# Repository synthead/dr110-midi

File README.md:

# Synthead BOSS DR-110 MIDI Retrofit

This is an open, Arduino-based project that adds MIDI to your BOSS DR-110!

## Features

This retrofit supports:

- **MIDI sync** via MIDI start, stop, continue, and beat clock messages to play patterns programmed on the DR-110's internal sequencer in time.
- **MIDI note on** messages to play individual drum sounds in an external sequencer.  The General MIDI note mapping is followed.

## How it works

### MIDI sync

The START and STOP buttons on the front panel are "pressed" to MIDI start and stop messages, and a clock is generated to keep the internal sequencer in time with MIDI beat clock messages.  There is also a transistor on the retrofit that restores the internal clock when MIDI sync is not being used.

### MIDI notes

The key matrix for the front panel was reverse-engineered, and this retrofit "presses" the buttons on incoming MIDI note on messages.  This means that it's also possible to program the DR-110's internal sequencer in tap write mode over MIDI using either the internal clock or while the sequencer is synchronized to MIDI sync messages.

## Building a board

The retrofit is built on a small, single-sided PCB using only generic, through-hole components.  This makes it more accessible for it to be built at home.  The copper and silkscreen renders can be found in the [`KiCad/rendered/`](https://github.com/synthead/dr110-midi/tree/master/KiCad/rendered/) directory.

The board needs to be built as low-profile as possible.  The transistors should have their legs bent at right angles, and the Arduino Pro Micro board should lay directly on the surface of the PCB, preferably with small pieces of solid wire connecting the PCBs together.

### Parts list

| Reference | Part number       |
|-----------|-------------------|
| Q1-7      | BC547             |
| R1-7      | 1-10K             |
| R8, 10    | 220               |
| R9        | 4.7K              |
| D1        | 1N4148            |
| U1        | 6N138             |
| U2        | Arduino Pro Micro |

When built, it'll produce a board like this:

## Installation

Solder stranded wire to the connections of J1 and solder them onto the solder joints as pictured below.  While doing so, separate the fourth wire off of the ribbon cable between the CPU and voice board with a razor blade, remove it, and solder CI and CO to the through holes.

Then, solder stranded wire to J2 and connect them to pins 4 and 5 of a female chassis mount DIN-5 connector for MIDI input.  It is also possible to mount a USB connection to the exterior of the DR-110 to provide updates to the retrofit without opening the unit (see the [Amphoenol MUSBB55104](https://www.arrow.com/en/products/musbb55104/amphenol) connector).

The DIN-5 and USB connectors fit neatly in the bottom-left corner of the DR-110 by the battery compartment.  The retrofit should be insulated, preferably with heatshrink.  It's a tight fit when installed and fits best with the position in the picture below.  Move it around slightly until it fits snug with the DR-110 components, then carefully close the machine.

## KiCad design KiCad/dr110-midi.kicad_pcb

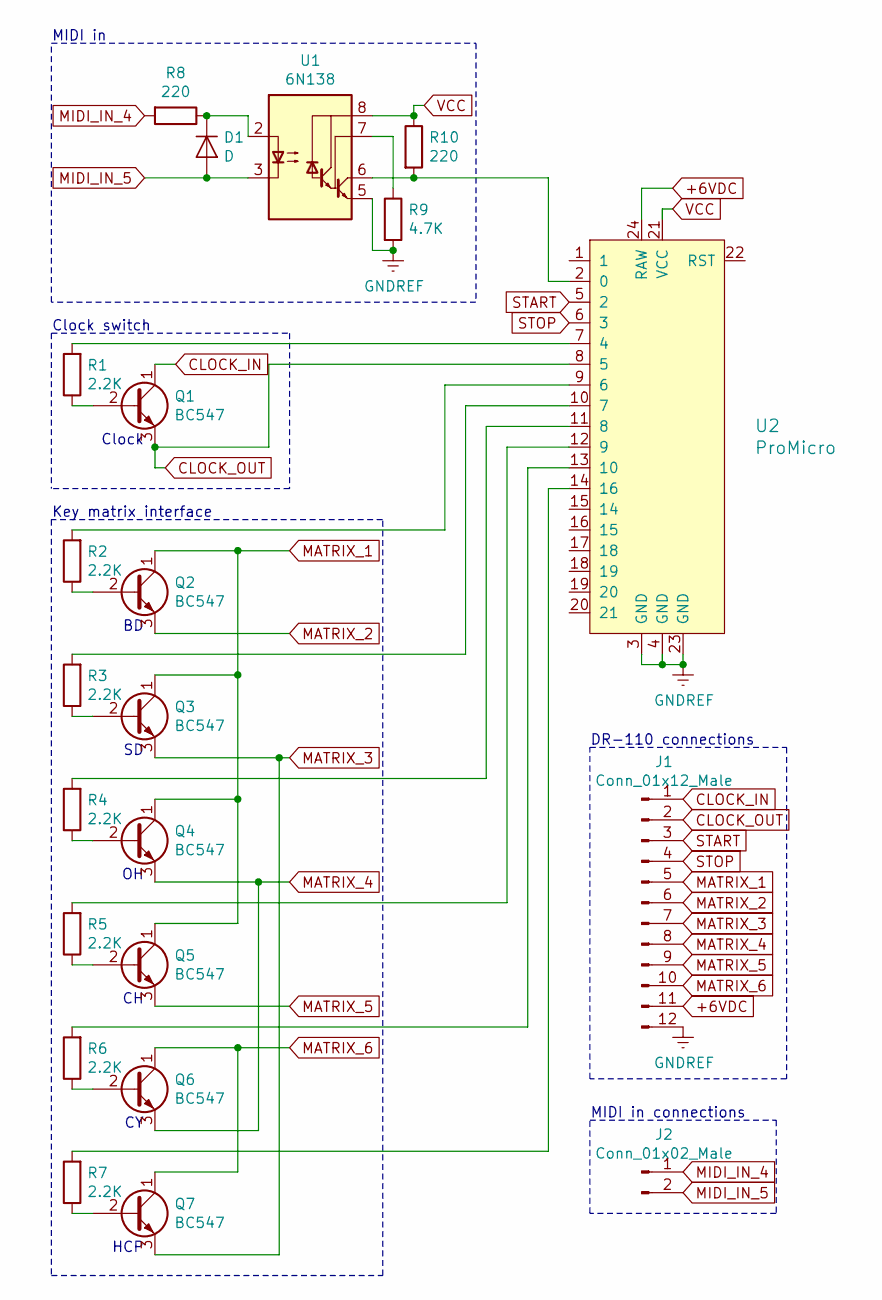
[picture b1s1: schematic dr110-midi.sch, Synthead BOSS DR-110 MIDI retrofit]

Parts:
D1: D; D_DO-35_SOD27_P5.08mm_Vertical_KathodeUp
J1: Conn_01x12_Male; Socket_Strip_Straight_1x12_Pitch2.54mm
J2: Conn_01x02_Male; Socket_Strip_Straight_1x02_Pitch2.54mm
Q1, Q2, Q3, Q4, Q5, Q6, Q7: BC547; TO-92_Molded_Wide
R1, R2, R3, R4, R5, R6, R7: 2.2K; R_Axial_DIN0204_L3.6mm_D1.6mm_P5.08mm_Horizontal
R8, R10: 220; R_Axial_DIN0204_L3.6mm_D1.6mm_P5.08mm_Horizontal
R9: 4.7K; R_Axial_DIN0204_L3.6mm_D1.6mm_P5.08mm_Horizontal
U1: 6N138; DIP-8_W7.62mm
U2: ProMicro

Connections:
+6VDC: J1.11, U2.24 (RAW)
CLOCK_IN: J1.1, Q1.1 (C)
CLOCK_OUT: J1.2, Q1.3 (E), U2.8 (5)
GNDREF: J1.12, R9.2, U1.5 (GND), U2.3 (GND), U2.4 (GND), U2.23 (GND)
MATRIX_1: J1.5, Q2.1 (C), Q3.1 (C), Q4.1 (C), Q5.1 (C)
MATRIX_2: J1.6, Q2.3 (E)
MATRIX_3: J1.7, Q3.3 (E), Q7.3 (E)
MATRIX_4: J1.8, Q4.3 (E), Q6.3 (E)
MATRIX_5: J1.9, Q5.3 (E)
MATRIX_6: J1.10, Q6.1 (C), Q7.1 (C)
MIDI_IN_4: J2.1, R8.2
MIDI_IN_5: D1.2 (A), J2.2, U1.3 (C2)
unnamed: D1.1 (K), R8.1, U1.2 (C1)
unnamed: Q1.2 (B), R1.1
unnamed: Q2.2 (B), R2.1
unnamed: Q3.2 (B), R3.1
unnamed: Q4.2 (B), R4.1
unnamed: Q5.2 (B), R5.1
unnamed: Q6.2 (B), R6.1
unnamed: Q7.2 (B), R7.1
unnamed: R1.2, U2.7 (4)
unnamed: R2.2, U2.9 (6)
unnamed: R3.2, U2.10 (7)
unnamed: R4.2, U2.11 (8)
unnamed: R5.2, U2.12 (9)
unnamed: R6.2, U2.13 (10)
unnamed: R7.2, U2.14 (16)
unnamed: R9.1, U1.7 (VO1)
unnamed: R10.2, U1.6 (VO2), U2.2 (0)
START: J1.3, U2.5 (2)
STOP: J1.4, U2.6 (3)
VCC: R10.1, U1.8 (VCC), U2.21 (VCC)

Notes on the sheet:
Clock switch
Clock
DR-110 connections
MIDI in
MIDI in connections
HCP
Key matrix interface

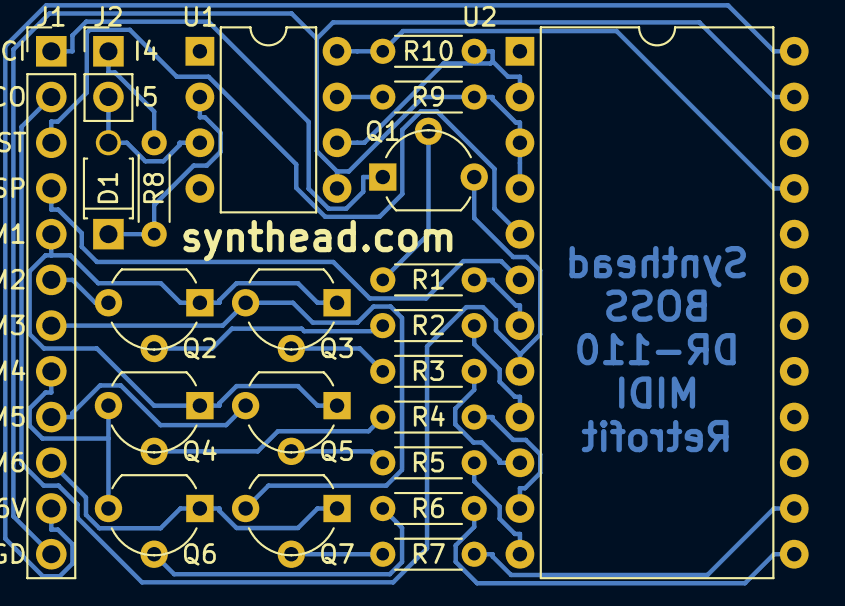
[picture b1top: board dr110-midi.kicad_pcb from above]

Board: 2 copper layers, 22 parts (0 on the bottom side), 32 nets.

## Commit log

2019-03-28 Initial commit.
2019-03-28 Rename set_int_clock to set_internal_clock.
2019-03-29 Trigger drums from MIDI note messages.
2019-04-03 Add KiCad project.
2019-04-04 Ignore MIDI clock when stopped.
2019-04-04 Fix key matrix transistor pinouts.
2019-04-04 Add silkscreen text for connection pinouts.
2019-04-04 Update fp-info-cache.
2019-04-06 Add drill guides to copper side.
2019-04-06 Add render of silkscreen with connector labels.
2019-04-22 Don't halt code when pressing buttons.
2019-04-22 Add README.md.
2019-04-22 Fix START and STOP buttons not being released.
2019-04-22 Use 50 ms button press time for START and STOP.
2019-04-22 Correct resistor references in parts list.
